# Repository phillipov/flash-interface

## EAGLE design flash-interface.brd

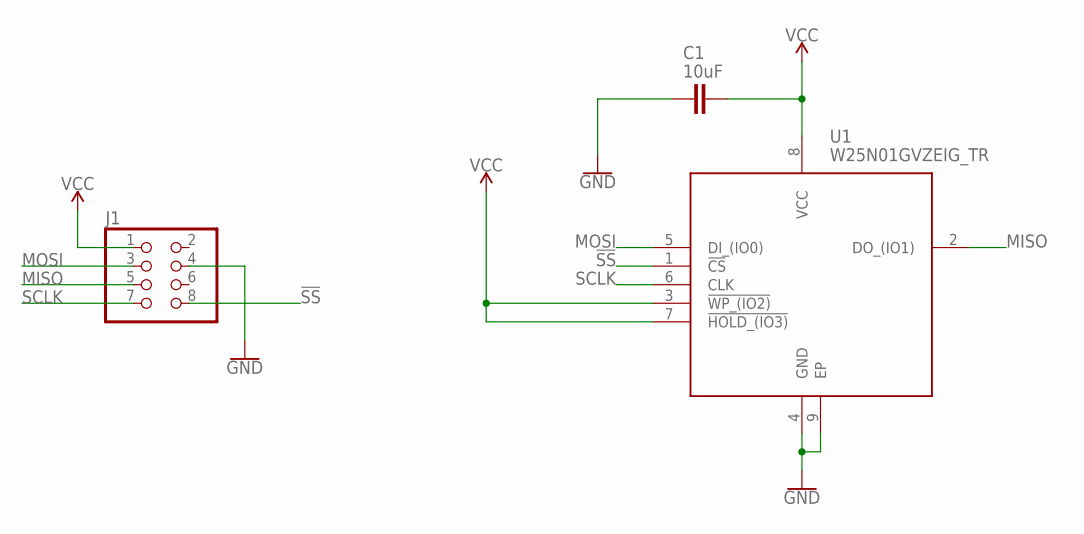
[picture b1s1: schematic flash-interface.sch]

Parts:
C1: 10uF; 0805
J1: PINHD-2X4; 2X04
U1: W25N01GVZEIG_TR; SON127P800X600X80-9N

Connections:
!SS: J1.8, U1.1 (!CS)
GND: C1.2, J1.4, U1.4 (GND), U1.9 (EP)
MISO: J1.5, U1.2 (DO_(IO1))
MOSI: J1.3, U1.5 (DI_(IO0))
SCLK: J1.7, U1.6 (CLK)
VCC: C1.1, J1.1, U1.3 (!WP_(IO2)), U1.7 (!HOLD_(IO3)), U1.8 (VCC)

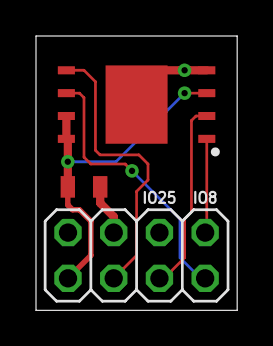
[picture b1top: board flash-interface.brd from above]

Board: 2 copper layers, 11.2 x 15.2 mm, 3 parts (0 on the bottom side), 6 nets.

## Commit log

2019-09-03 Started the schematic with the STM32L4 and Winbond flash IC
2019-09-04 Added bare minimum components for both ICs
2019-09-05 Added SWD debug connector to STM32
2019-09-05 Replaced STM32 system with a Raspberry Pi SPI header
2019-09-05 Laid out a board file
2019-09-05 Replaced 0603 cap with 0805, fully routed board
2019-09-05 Gave the ground plane more room

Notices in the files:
parts and their libraries:
SparkFun-Capacitors: Licensing: Creative Commons ShareAlike 4.0 International - https://creativecommons.org/licenses/by-sa/4.0
